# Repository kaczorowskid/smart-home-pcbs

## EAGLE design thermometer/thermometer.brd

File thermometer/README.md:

## Wireless Thermometer

### Schematic:

### PCB:

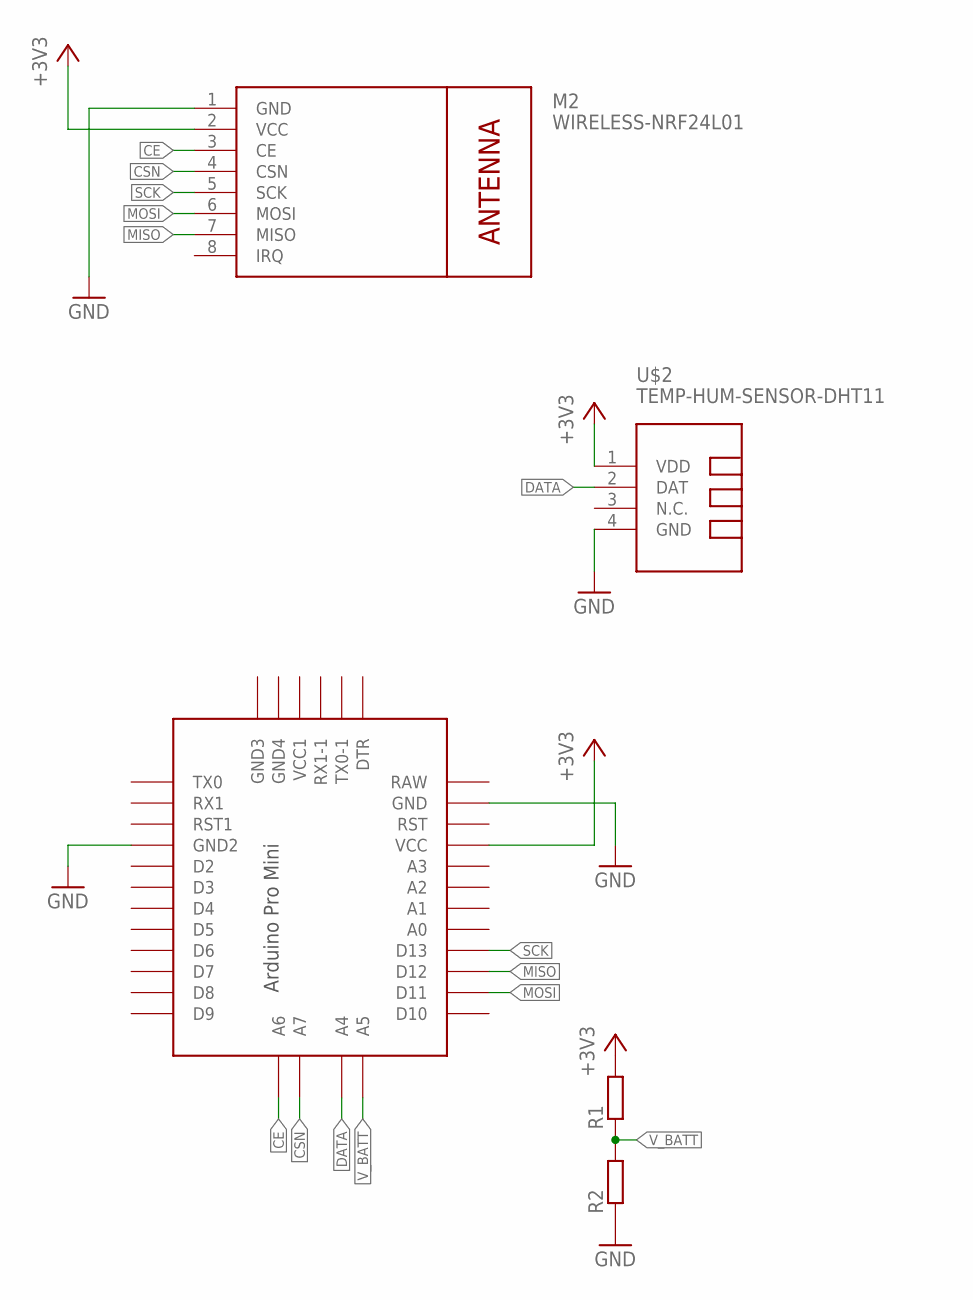
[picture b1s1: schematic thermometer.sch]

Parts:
M2: WIRELESS-NRF24L01
R1, R2: R-EU_R0805; R0805
U$2: TEMP-HUM-SENSOR-DHT11
U$3: PRO-MINI-2

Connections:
+3V3: M2.2 (VCC), R1.2, U$2.1 (VDD), U$3.VCC
CE: M2.3 (CE), U$3.A6
CSN: M2.4 (CSN), U$3.A7
DATA: U$2.2 (DAT), U$3.A4
GND: M2.1 (GND), R2.1, U$2.4 (GND), U$3.GND, U$3.GND1 (GND2)
MISO: M2.7 (MISO), U$3.D12
MOSI: M2.6 (MOSI), U$3.D11
SCK: M2.5 (SCK), U$3.D13
V_BATT: R1.1, R2.2, U$3.A5

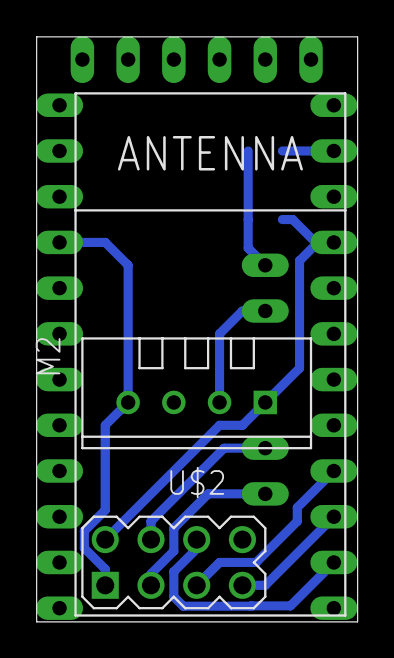
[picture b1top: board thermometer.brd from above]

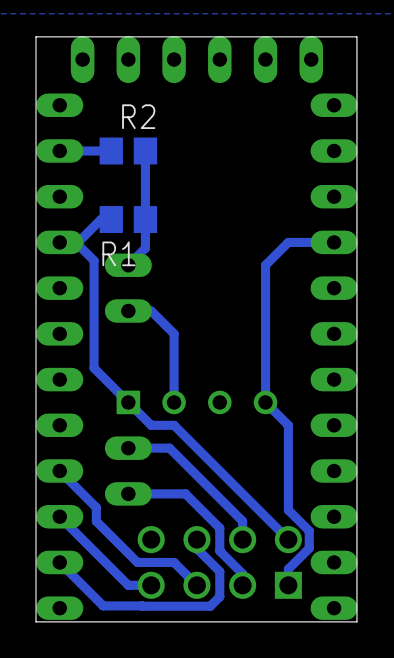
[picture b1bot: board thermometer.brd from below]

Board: 2 copper layers, 17.8 x 32.5 mm, 5 parts (2 on the bottom side), 9 nets.

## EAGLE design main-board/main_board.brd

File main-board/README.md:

## Central Controller for Wireless Devices

### Schematic:

### PCB:

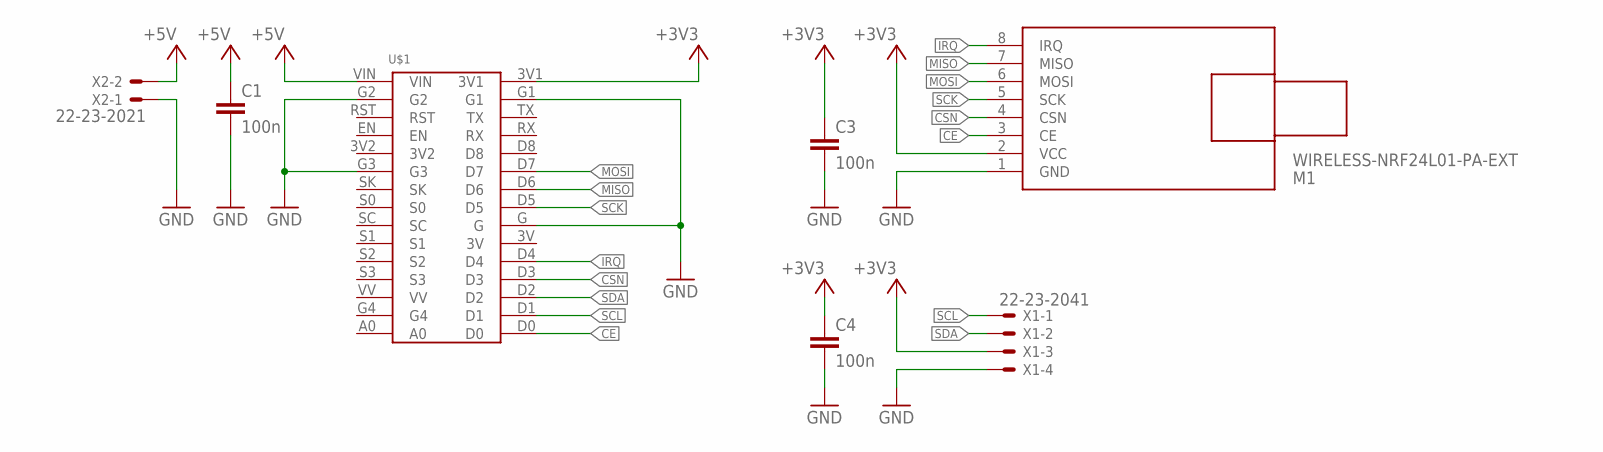
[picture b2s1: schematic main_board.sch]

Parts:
C1, C3, C4: 100n; C0805
M1: WIRELESS-NRF24L01-PA-EXT
U$1: LOLIN
X1: 22-23-2041
X2: 22-23-2021

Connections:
+3V3: C3.1, C4.1, M1.2 (VCC), U$1.3V1, X1.3
+5V: C1.1, U$1.VIN, X2.2
CE: M1.3 (CE), U$1.D0
CSN: M1.4 (CSN), U$1.D3
GND: C1.2, C3.2, C4.2, M1.1 (GND), U$1.G, U$1.G1, U$1.G2, U$1.G3, X1.4, X2.1
IRQ: M1.8 (IRQ), U$1.D4
MISO: M1.7 (MISO), U$1.D6
MOSI: M1.6 (MOSI), U$1.D7
SCK: M1.5 (SCK), U$1.D5
SCL: U$1.D1, X1.1
SDA: U$1.D2, X1.2

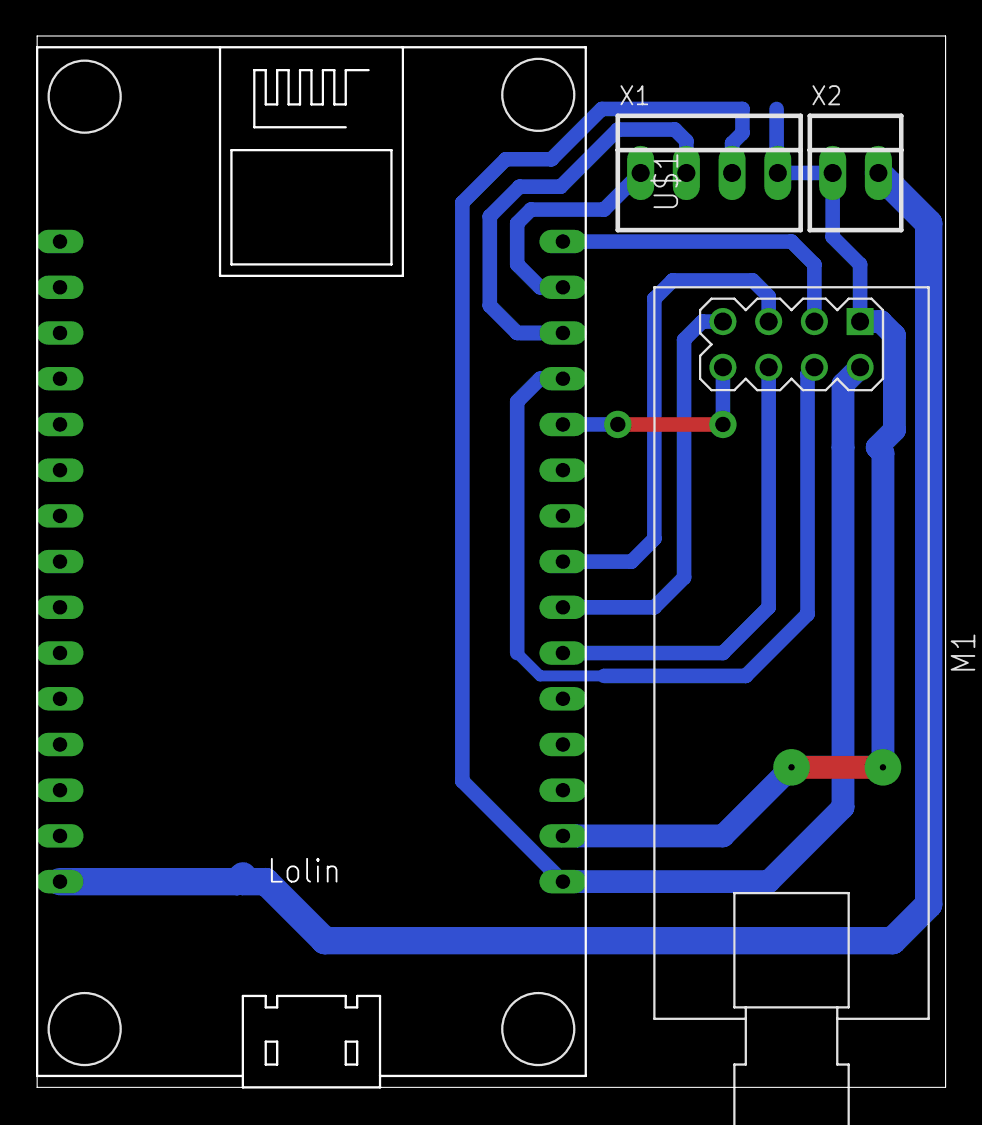
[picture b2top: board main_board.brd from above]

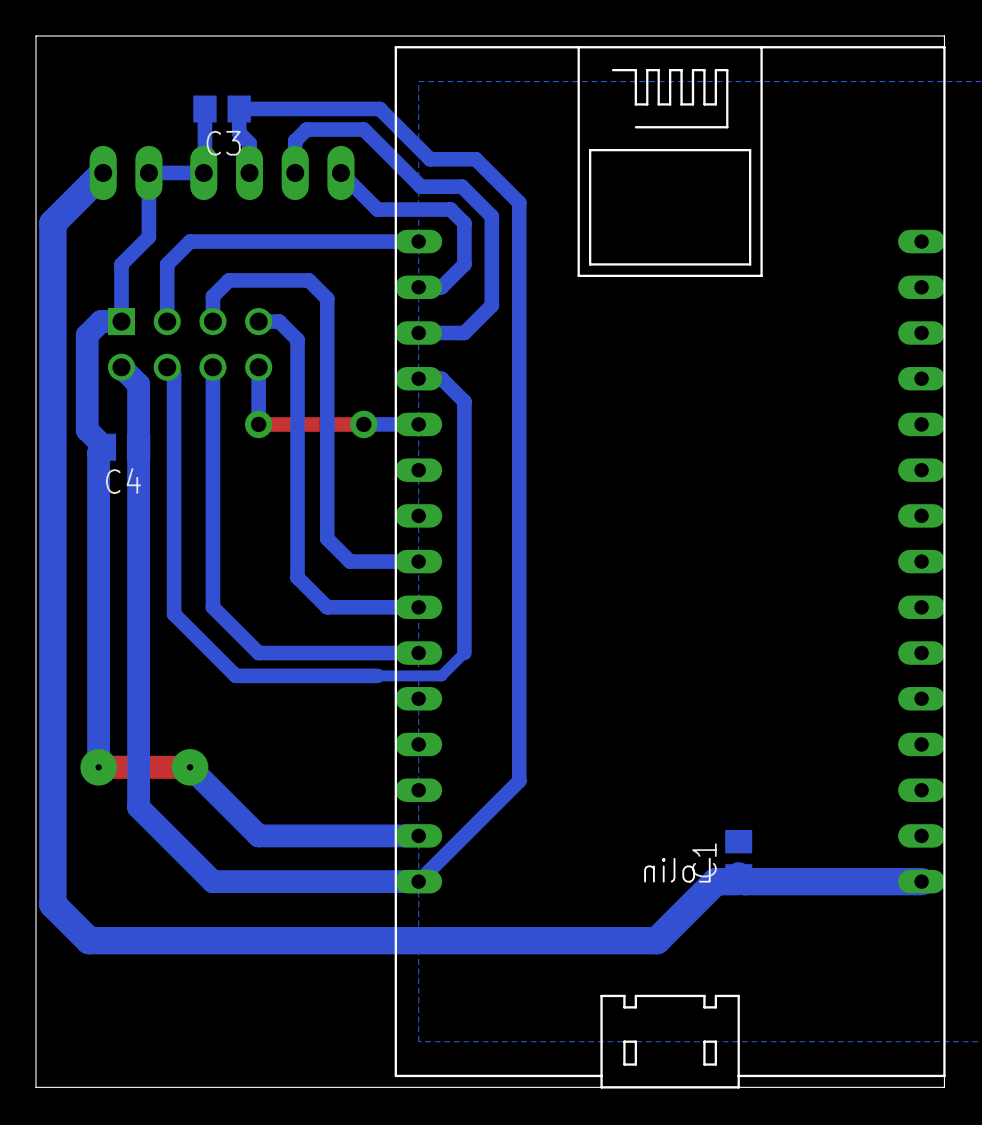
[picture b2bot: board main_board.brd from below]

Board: 2 copper layers, 50.5 x 58.4 mm, 7 parts (3 on the bottom side), 11 nets.

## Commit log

2024-12-11 feat: add main-board pcb
2024-12-16 feat: add thermometer
2025-01-09 docs: add readme file

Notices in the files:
parts and their libraries:
diy-modules: Released under the Creative Commons Attribution 4.0 International License: http://creativecommons.org/licenses/by/4.0
